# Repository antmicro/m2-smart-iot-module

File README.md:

# M.2 Smart IoT Module

Copyright (c) 2020-2026 [Antmicro](https://www.antmicro.com)

## Overview

This project contains PCB design files of the smart IoT module in an M.2 form factor.
The module is an experimental platform that combines a programmable Nordic radio SoC with Google Coral Edge AI accelerator.
The design files were prepared in KiCad.

## Repository structure

The main repository directory contains KiCad PCB project files, a LICENSE and a README.
The remaining files are stored in the following directories:

* ``lib`` - contains the component libraries
* ``img`` - contains graphics for this README
* ``fab`` - contains overrides for board visualization

## Key Features

* Google Coral Edge TPU Accelerator Module
* Nordic Semiconductor nRF52840 Radio SoC
* On-board PCIe-USB bridge
* On-board FTDI chip for nRF52840 programming, debugging and serial communication
* M.2 key B+M form factor 
* 22 x 80 mm (0.87 x 3.15 inch) PCB outline

## License

[Apache-2.0](LICENSE)

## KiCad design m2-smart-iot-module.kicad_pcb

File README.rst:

====================
M.2 Smart IoT Module
====================

Copyright (c) 2020-2021 `Antmicro <https://www.antmicro.com>`_

.. figure:: img/m2-smart-iot-module.png

Overview
--------

This repository contains design files of the smart IoT module in an M.2 form factor.
The module is an experimental platform that combines a programmable Nordic radio SoC with Google Coral Edge AI accelerator.
The design files were prepared in KiCad.
An initial production release for the design was fabricated as prototypes and these are now being tested.

Repository structure
--------------------
The main repository directory contains KiCad PCB project files, a LICENSE and README.
The remaining files are stored in the following directories:

* ``lib`` - contains the component libraries
* ``img`` - contains graphics for this README

Key Features
------------

* M.2 key B+M form factor 
* on-board PCIe-USB bridge
* Nordic Semiconductor nRF52840 Radio SoC
* Google Coral Edge TPU Accelerator Module

Block diagram
-------------

.. figure:: img/block-diagram.jpg

License
=======

`Apache-2.0 <LICENSE>`_

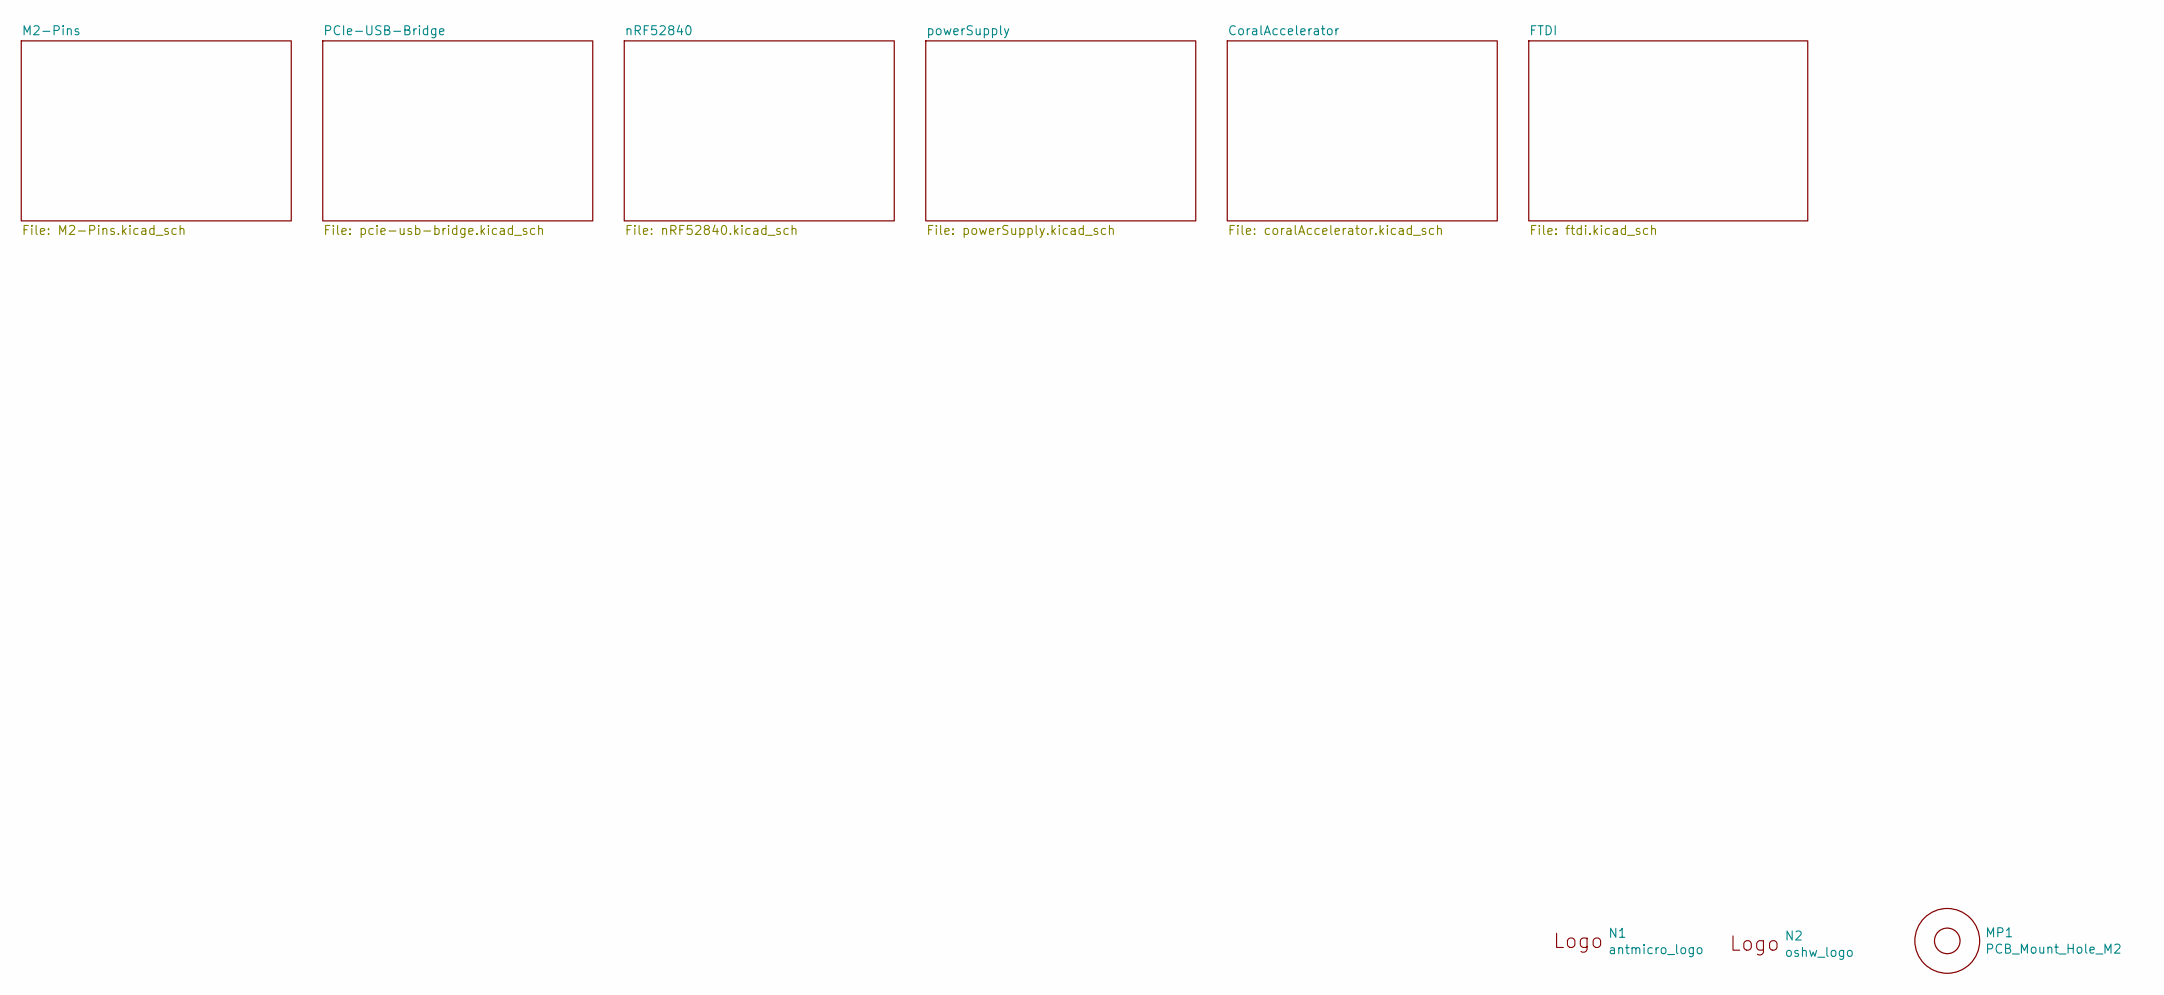
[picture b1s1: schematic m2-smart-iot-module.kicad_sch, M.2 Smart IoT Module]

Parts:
MP1: PCB_Mount_Hole_M2; M.2-Stud
N1: antmicro_logo; antmicro-logo_scaled_12mm
N2: oshw_logo; OSHW-Logo2_7.3x6mm_Copper_Mask

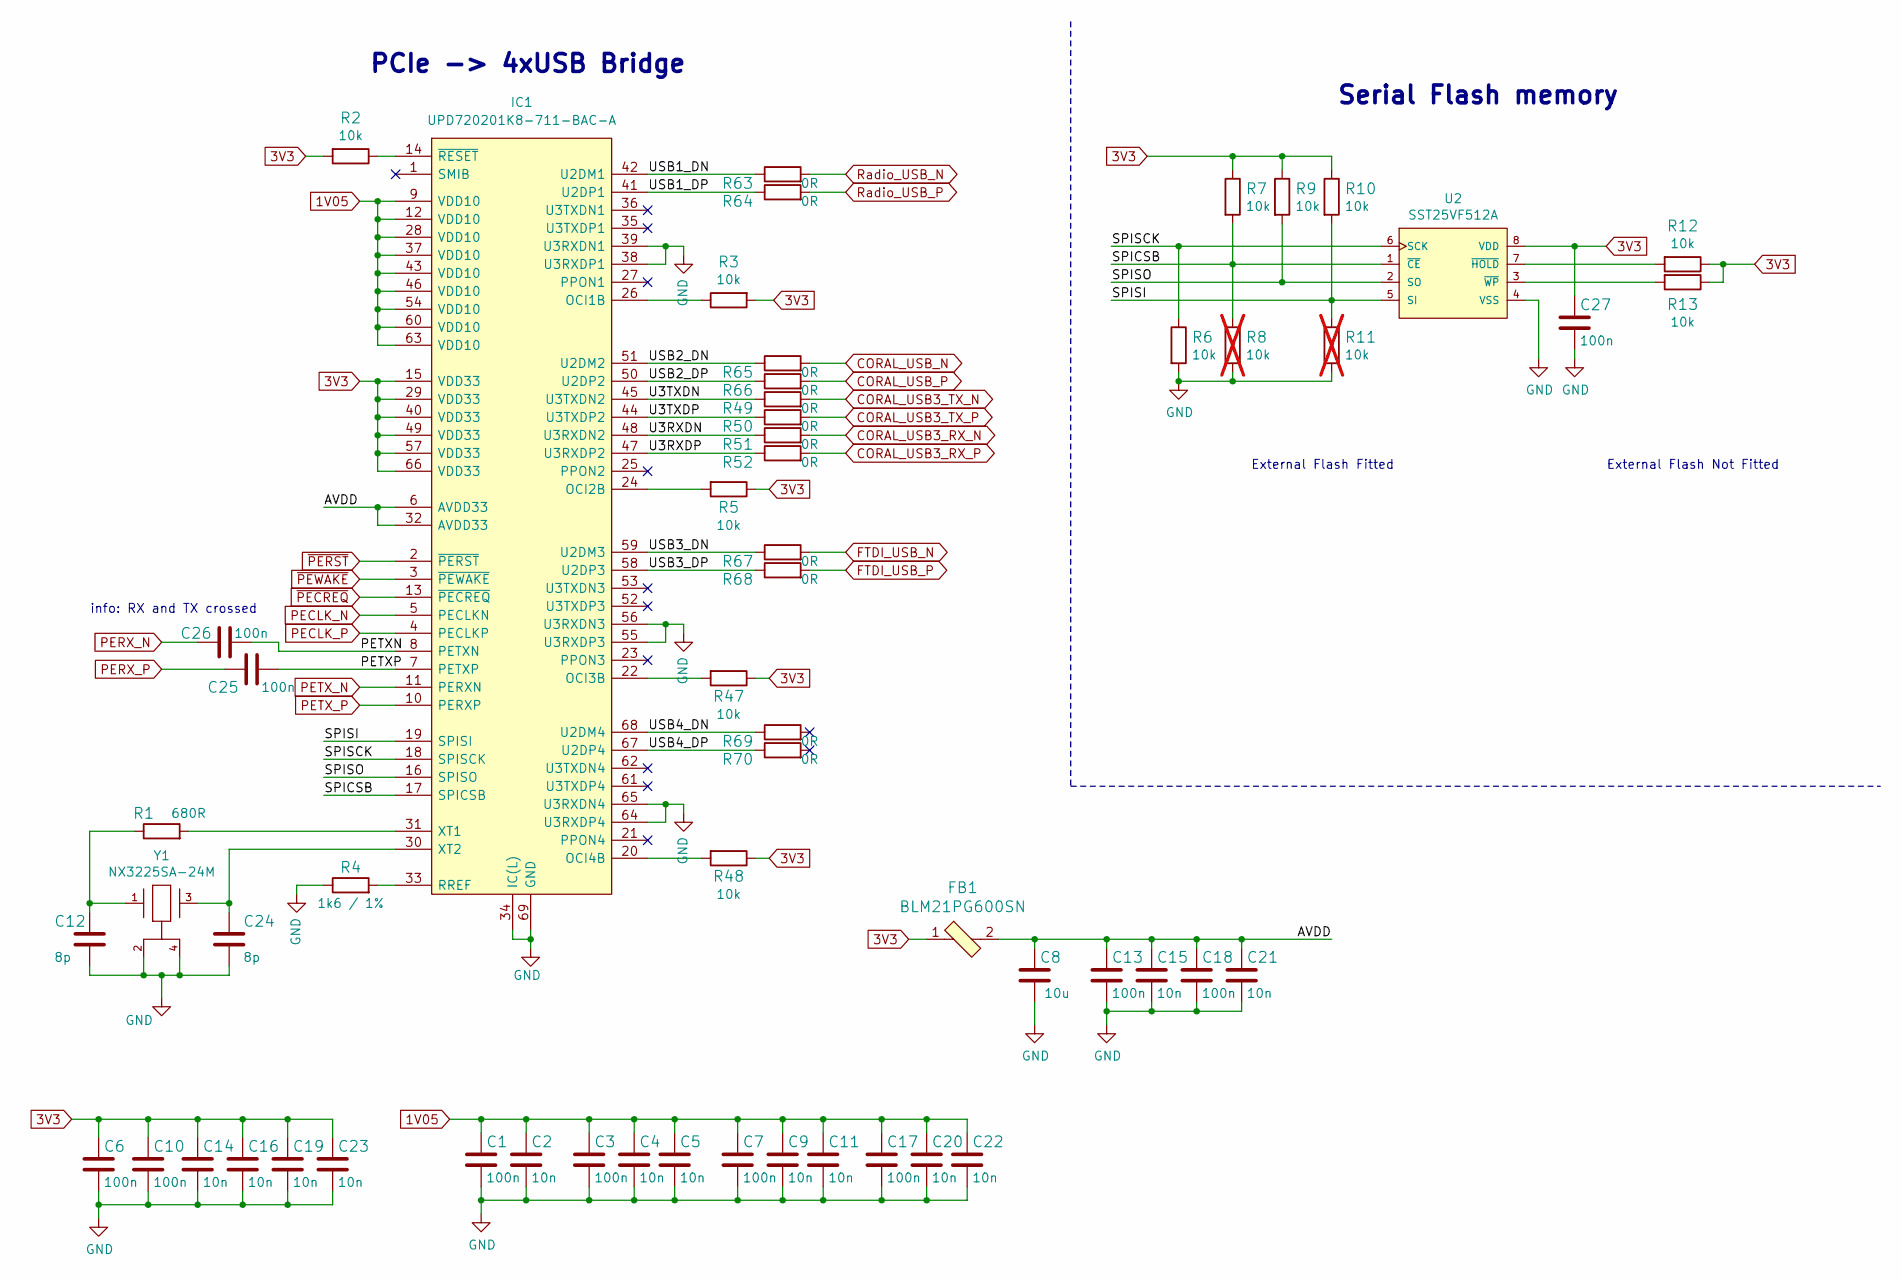
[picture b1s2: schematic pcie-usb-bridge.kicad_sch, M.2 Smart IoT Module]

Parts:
C1, C3, C6, C7, C10, C13, C17, C18, C25, C26, C27: C_100n_0402; 0402-cap; MPN GRM155R61H104KE14D
C2, C4, C5, C9, C11, C14, C15, C16, C19, C20, C21, C22, C23: C_10n_0402; 0402-cap; MPN 04025G103ZAT2A
C8: C_10u_0805; 0805-cap; MPN 160R15X106KV4E
C12, C24: C_8p_0402; 0402-cap; MPN CGA2B2C0G1H080D050BA
FB1: BLM21PG600SN; 0805-res; MPN BLM21PG600SN1
IC1: UPD720201K8-711-BAC-A; QFN40P800X800X90-69N-D; MPN UPD720201K8-711-BAC-A
R1: R_680R_0402; 0402-res; MPN MCWR04X6800FTL
R2, R3, R5, R6, R7, R9, R10, R12, R13: R_10k_0402; 0402-res; MPN CRCW040210K0FKEDHP
R4: R_1k6_0402; 0402-res; MPN MCWR04X1601FTL
R8, R11: R_10k_0402; 0402-res; MPN CRCW040210K0FKEDHP; not fitted
R47, R48: 0402-res; MPN CRCW040210K0FKEDHP
R49, R50, R51, R52, R63, R64, R65, R66, R67, R68, R69, R70: R_0R_0402; 0402-res; MPN ERJ2GE0R00X
U2: SST25VF512A; SOIC8-SST25VF512A-33-4I-SAE-Level_B; MPN SST25VF512A-33-4I-SAE
Y1: NX3225SA-24M; NDK-NX3225SA-0-0-MFG; MPN NX3225SA-24.000M-STD-CSR-3

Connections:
1V05: C1.1, C2.1, C3.1, C4.1, C5.1, C7.1, C9.1, C11.1, C17.1, C20.1, C22.1, IC1.9 (VDD10), IC1.12 (VDD10), IC1.28 (VDD10), IC1.37 (VDD10), IC1.43 (VDD10), IC1.46 (VDD10), IC1.54 (VDD10), IC1.60 (VDD10), IC1.63 (VDD10); also elsewhere on the board
3V3: C6.1, C10.1, C14.1, C16.1, C19.1, C23.1, C27.1, FB1.1, IC1.15 (VDD33), IC1.29 (VDD33), IC1.40 (VDD33), IC1.49 (VDD33), IC1.57 (VDD33), IC1.66 (VDD33), R2.2, R3.2, R5.1, R7.1, R9.1, R10.1, R12.1, R13.1, R47.1, R48.1, U2.8 (VDD); also elsewhere on the board
/PCIe-USB-Bridge/AVDD: C8.1, C13.1, C15.1, C18.1, C21.1, FB1.2, IC1.6 (AVDD33), IC1.32 (AVDD33)
/PCIe-USB-Bridge/PETXN: C26.1, IC1.8 (PETXN)
/PCIe-USB-Bridge/PETXP: C25.1, IC1.7 (PETXP)
/PCIe-USB-Bridge/SPICSB: IC1.17 (SPICSB), R7.2, R8.1, U2.1 (~CE)
/PCIe-USB-Bridge/SPISCK: IC1.18 (SPISCK), R6.1, U2.6 (SCK)
/PCIe-USB-Bridge/SPISI: IC1.19 (SPISI), R10.2, R11.1, U2.5 (SI)
/PCIe-USB-Bridge/SPISO: IC1.16 (SPISO), R9.2, U2.2 (SO)
/PCIe-USB-Bridge/U3RXDN: IC1.48 (U3RXDN2), R51.1
/PCIe-USB-Bridge/U3RXDP: IC1.47 (U3RXDP2), R52.1
/PCIe-USB-Bridge/U3TXDN: IC1.45 (U3TXDN2), R49.1
/PCIe-USB-Bridge/U3TXDP: IC1.44 (U3TXDP2), R50.1
/PCIe-USB-Bridge/USB1_DN: IC1.42 (U2DM1), R63.1
/PCIe-USB-Bridge/USB1_DP: IC1.41 (U2DP1), R64.1
/PCIe-USB-Bridge/USB2_DN: IC1.51 (U2DM2), R65.1
/PCIe-USB-Bridge/USB2_DP: IC1.50 (U2DP2), R66.1
/PCIe-USB-Bridge/USB3_DN: IC1.59 (U2DM3), R67.1
/PCIe-USB-Bridge/USB3_DP: IC1.58 (U2DP3), R68.1
/PCIe-USB-Bridge/USB4_DN: IC1.68 (U2DM4), R69.1
/PCIe-USB-Bridge/USB4_DP: IC1.67 (U2DP4), R70.1
CORAL_USB3_RX_N: R51.2
CORAL_USB3_RX_P: R52.2
CORAL_USB3_TX_N: R49.2
CORAL_USB3_TX_P: R50.2
CORAL_USB_N: R65.2; also elsewhere on the board
CORAL_USB_P: R66.2; also elsewhere on the board
FTDI_USB_N: R67.2; also elsewhere on the board
FTDI_USB_P: R68.2; also elsewhere on the board
GND: C1.2, C2.2, C3.2, C4.2, C5.2, C6.2, C7.2, C8.2, C9.2, C10.2, C11.2, C12.2, C13.2, C14.2, C15.2, C16.2, C17.2, C18.2, C19.2, C20.2, C21.2, C22.2, C23.2, C24.2, C27.2, IC1.34 (IC(L)), IC1.38 (U3RXDP1), IC1.39 (U3RXDN1), IC1.55 (U3RXDP3), IC1.56 (U3RXDN3), IC1.64 (U3RXDP4), IC1.65 (U3RXDN4), IC1.69 (GND), R4.1, R6.2, R8.2, R11.2, U2.4 (VSS), Y1.2 (GND), Y1.4 (GND); also elsewhere on the board
unnamed: C12.1, R1.1, Y1.1
unnamed: C24.1, IC1.30 (XT2), Y1.3
unnamed: IC1.14 (~RESET), R2.1
unnamed: IC1.20 (OCI4B), R48.2
unnamed: IC1.22 (OCI3B), R47.2
unnamed: IC1.24 (OCI2B), R5.2
unnamed: IC1.26 (OCI1B), R3.1
unnamed: IC1.31 (XT1), R1.2
unnamed: IC1.33 (RREF), R4.2
unnamed: R12.2, U2.7 (~HOLD)
unnamed: R13.2, U2.3 (~WP)
PECLK_N: IC1.5 (PECLKN); also elsewhere on the board
PECLK_P: IC1.4 (PECLKP); also elsewhere on the board
PERX_N: C26.2; also elsewhere on the board
PERX_P: C25.2; also elsewhere on the board
PETX_N: IC1.11 (PERXN); also elsewhere on the board
PETX_P: IC1.10 (PERXP); also elsewhere on the board
Radio_USB_N: R63.2; also elsewhere on the board
Radio_USB_P: R64.2; also elsewhere on the board
~PECREQ: IC1.13 (~PECREQ); also elsewhere on the board
~PERST: IC1.2 (~PERST); also elsewhere on the board
~PEWAKE: IC1.3 (~PEWAKE); also elsewhere on the board

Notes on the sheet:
Serial Flash memory
External Flash Not Fitted
PCIe -> 4xUSB Bridge
External Flash Fitted
info: RX and TX crossed

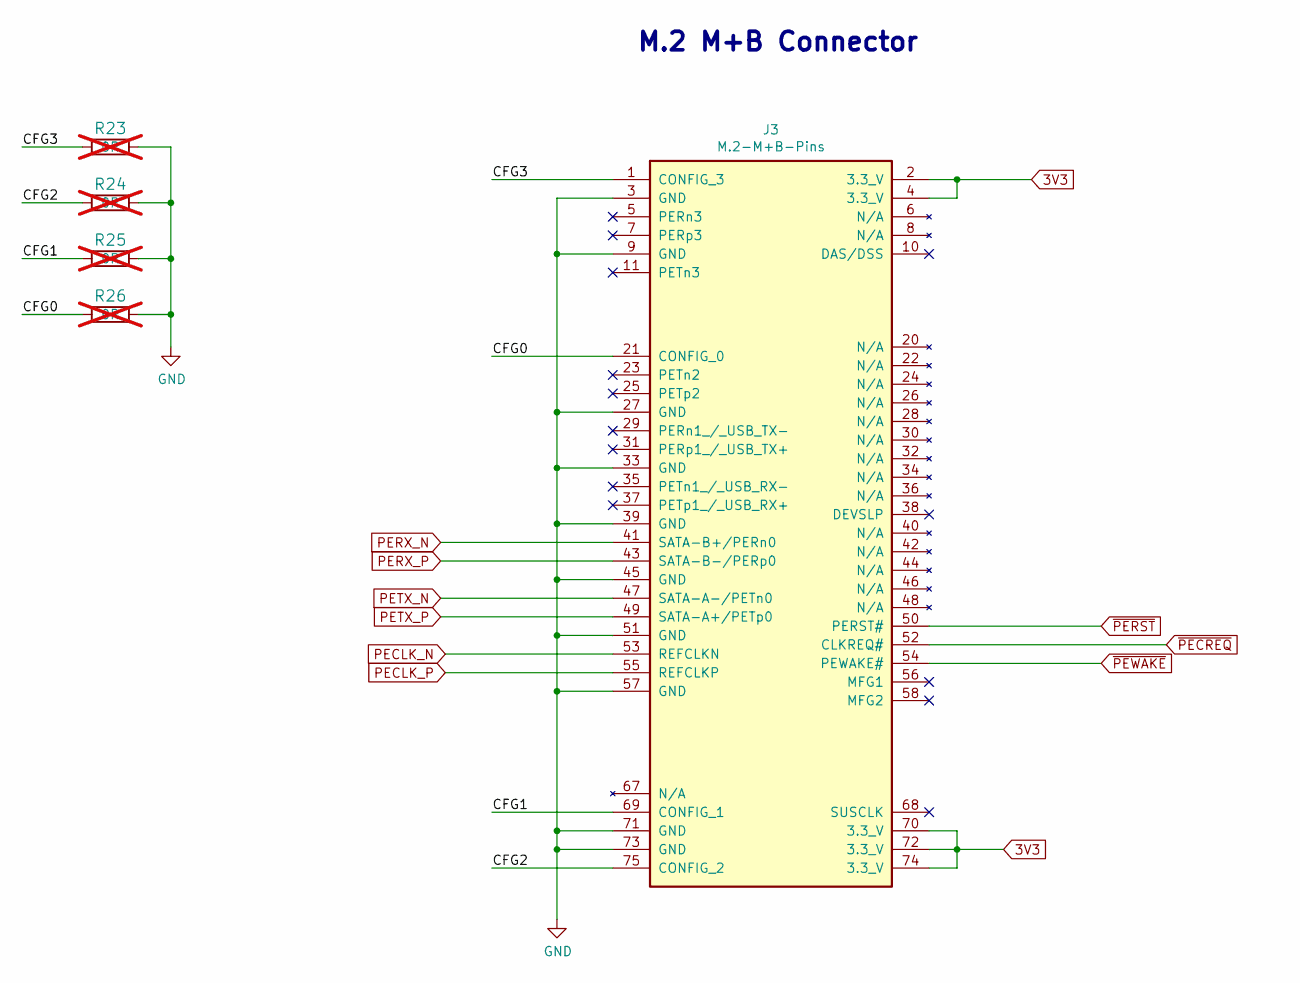
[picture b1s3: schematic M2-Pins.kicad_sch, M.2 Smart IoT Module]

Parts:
J3: M.2-M+B-Pins; M.2-M+B-Keys
R23, R24, R25, R26: R_0R_0402; 0402-res; MPN ERJ2GE0R00X; not fitted

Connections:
3V3: J3.2 (3.3_V), J3.4 (3.3_V), J3.70 (3.3_V), J3.72 (3.3_V), J3.74 (3.3_V); also elsewhere on the board
/M2-Pins/CFG0: J3.21 (CONFIG_0), R26.1
/M2-Pins/CFG1: J3.69 (CONFIG_1), R25.1
/M2-Pins/CFG2: J3.75 (CONFIG_2), R24.1
/M2-Pins/CFG3: J3.1 (CONFIG_3), R23.1
GND: J3.3 (GND), J3.9 (GND), J3.27 (GND), J3.33 (GND), J3.39 (GND), J3.45 (GND), J3.51 (GND), J3.57 (GND), J3.71 (GND), J3.73 (GND), R23.2, R24.2, R25.2, R26.2; also elsewhere on the board
PECLK_N: J3.53 (REFCLKN); also elsewhere on the board
PECLK_P: J3.55 (REFCLKP); also elsewhere on the board
PERX_N: J3.41 (SATA-B+/PERn0); also elsewhere on the board
PERX_P: J3.43 (SATA-B-/PERp0); also elsewhere on the board
PETX_N: J3.47 (SATA-A-/PETn0); also elsewhere on the board
PETX_P: J3.49 (SATA-A+/PETp0); also elsewhere on the board
~PECREQ: J3.52 (CLKREQ#); also elsewhere on the board
~PERST: J3.50 (PERST#); also elsewhere on the board
~PEWAKE: J3.54 (PEWAKE#); also elsewhere on the board

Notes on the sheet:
M.2 M+B Connector

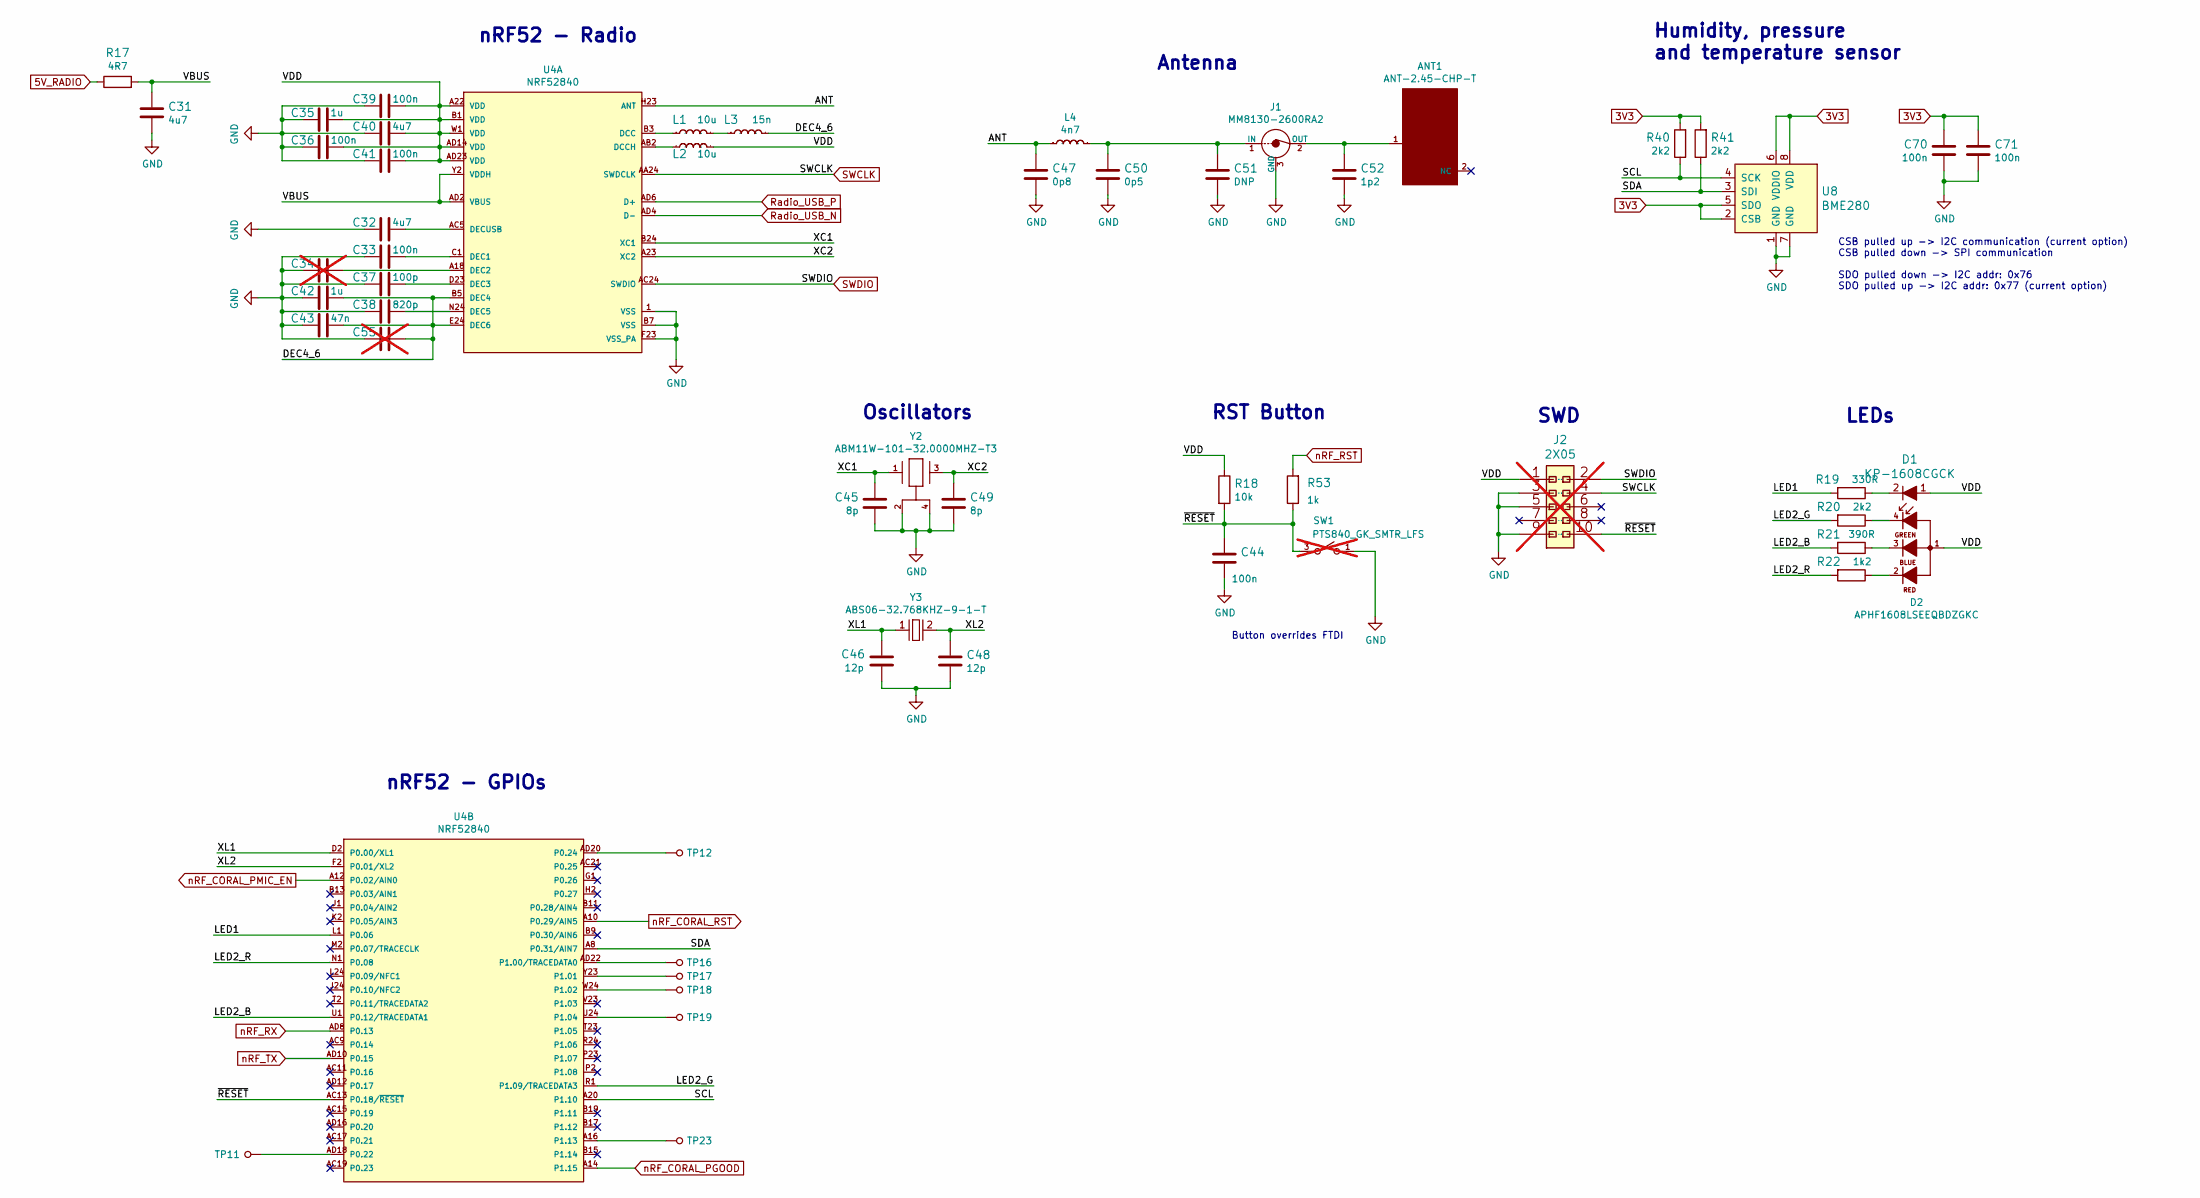
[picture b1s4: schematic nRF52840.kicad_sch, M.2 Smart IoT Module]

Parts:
ANT1: ANT-2.45-CHP-T; Linx-ANT-2.45-CHP-T-MFG; MPN ANT-2.45-CHP-T
C31, C32, C40: C_4u7_0402; 0402-cap; MPN GRM155R61A475MEAAD
C33, C36, C39, C41, C44, C70, C71: C_100n_0402; 0402-cap; MPN GRM155R61H104KE14D
C34, C55: C_100n_0402; 0402-cap; MPN 0402X104K6R3CT; not fitted
C35, C42: C_1u_0402; 0402-cap; MPN C1005X6S1A105K050BC
C37: C_100p_0402; 0402-cap; MPN 0402N101J500CT
C38: C_820p_0402; 0402-cap; MPN CGA2B2C0G1H821J050BA
C43: C_47n_0402; 0402-cap; MPN MC0402X473K160CT
C45, C49: C_8p_0402; 0402-cap; MPN CGA2B2C0G1H080D050BA
C46, C48: C_12p_0402; 0402-cap; MPN CGA2B2C0G1H120J050BA
C47: C_0p8_0402; 0402-cap; MPN GJM1555C1HR80WB01D
C50: C_0p5_0402; 0402-cap; MPN GJM1555C1HR50WB01D
C51: RF_Capacitor; 0402-cap
C52: C_1p2_0402; 0402-cap; MPN GJM1555C1H1R2WB01D
D1: KP-1608CGCK; LED0603; MPN KP-1608CGCK
D2: APHF1608LSEEQBDZGKC; LED_APHF1608LSEEQBDZGKC; MPN APHF1608LSEEQBDZGKC
J1: MM8130-2600RA2; Murata-MM8130-2600RA2-MFG; MPN MM8130-2600RA2
J2: 2X05; ARM_SWD; MPN SHF-105-01-L-D-SM; not fitted
L1: L_10u_250mA_0603; 0603-res; MPN MLZ1608M100WTD25
L2: L_10u_80mA_0603; 0603-res; MPN LBMF1608T100K
L3: L_15n_0402; 0402-res; MPN HK100515NJ-T
L4: L_4n7_0402; 0402-res; MPN MCFT000004
R17: R_4R7_0402; 0402-res; MPN ERJ2GEJ4R7X
R18: R_10k_0402; 0402-res; MPN CRCW040210K0FKEDHP
R19: R_330R_0402; 0402-res; MPN ERJ2RKF3300X
R20, R40, R41: R_2k2_0402; 0402-res; MPN RC0402FR-072K2L
R21: R_390R_0402; 0402-res; MPN ERJ2RKF3900X
R22: R_1k2_0402; 0402-res; MPN ERJ2RKF1201X
R53: R_1k_0402; 0402-res; MPN CR0402-FX-1001GLF
SW1: PTS840_GK_SMTR_LFS; CK-PTS840_GK_SMTR_LFS-0; MPN PTS840 GK SMTR LFS; not fitted
TP11, TP12, TP16, TP17, TP18, TP19, TP23: TP_SMD1MM; Testpoint_smd_1mm
U4: NRF52840; Nordic_Semiconductor-NRF52840-QIAA-R-0-0-MFG; MPN NRF52840-QIAA-R
U8: BME280; Pressure_Sensor_LGA-8_2.5x2.5mm_BME280; MPN BME280
Y2: ABM11W-101-32.0000MHZ-T3; Abracon-ABM11W-0-0-0; MPN ABM11W-101-32.0000MHZ-T3
Y3: ABS06-32.768KHZ-9-1-T; Abracon-ABS06-32.768KHZ-T-0; MPN ABS06-32.768KHZ-9-1-T

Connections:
3V3: C70.2, C71.1, R40.2, R41.2, U8.2 (CSB), U8.5 (SDO), U8.6 (VDDIO), U8.8 (VDD); also elsewhere on the board
5V_RADIO: R17.1; also elsewhere on the board
/nRF52840/ANT: C47.1, L4.1, U4.H23 (ANT)
/nRF52840/DEC4_6: C42.1, C43.1, C55.1, L3.2, U4.B5 (DEC4), U4.E24 (DEC6)
/nRF52840/LED1: R19.2, U4.L1 (P0.06)
/nRF52840/LED2_B: R21.2, U4.U1 (P0.12/TRACEDATA1)
/nRF52840/LED2_G: R20.2, U4.R1 (P1.09/TRACEDATA3)
/nRF52840/LED2_R: R22.2, U4.N1 (P0.08)
/nRF52840/SCL: R40.1, U4.A20 (P1.10), U8.4 (SCK)
/nRF52840/SDA: R41.1, U4.A8 (P0.31/AIN7), U8.3 (SDI)
/nRF52840/VBUS: C31.1, R17.2, U4.AD2 (VBUS), U4.Y2 (VDDH)
/nRF52840/VDD: C35.1, C36.1, C39.1, C40.1, C41.1, D1.1, D2.1, J2.1, L2.2, R18.1, U4.A22 (VDD), U4.AD14 (VDD), U4.AD23 (VDD), U4.B1 (VDD), U4.W1 (VDD)
/nRF52840/XC1: C45.1, U4.B24 (XC1), Y2.1
/nRF52840/XC2: C49.1, U4.A23 (XC2), Y2.3
/nRF52840/XL1: C46.1, U4.D2 (P0.00/XL1), Y3.1
/nRF52840/XL2: C48.1, U4.F2 (P0.01/XL2), Y3.2
/nRF52840/~RESET: C44.1, J2.10, R18.2, R53.1, SW1.3, SW1.4, U4.AC13 (P0.18/~RESET)
GND: C31.2, C32.2, C33.2, C34.2, C35.2, C36.2, C37.2, C38.2, C39.2, C40.2, C41.2, C42.2, C43.2, C44.2, C45.2, C46.2, C47.2, C48.2, C49.2, C50.2, C51.2, C52.2, C55.2, C70.1, C71.2, J1.3 (GND), J1.4 (GND), J1.5 (GND), J1.6 (GND), J2.3, J2.5, J2.9, SW1.1, SW1.2, U4.1 (VSS), U4.B7 (VSS), U4.F23 (VSS_PA), U8.1 (GND), U8.7 (GND), Y2.2 (GND), Y2.4 (GND); also elsewhere on the board
unnamed: ANT1.1 (FEED), C52.1, J1.2 (OUT)
unnamed: C32.1, U4.AC5 (DECUSB)
unnamed: C33.1, U4.C1 (DEC1)
unnamed: C34.1, U4.A18 (DEC2)
unnamed: C37.1, U4.D23 (DEC3)
unnamed: C38.1, U4.N24 (DEC5)
unnamed: C50.1, C51.1, J1.1 (IN), L4.2
unnamed: D1.2, R19.1
unnamed: D2.2, R22.1
unnamed: D2.3, R21.1
unnamed: D2.4, R20.1
unnamed: L1.1, U4.B3 (DCC)
unnamed: L1.2, L3.1
unnamed: L2.1, U4.AB2 (DCCH)
unnamed: TP11.1, U4.AD18 (P0.22)
unnamed: TP12.1, U4.AD20 (P0.24)
unnamed: TP16.1, U4.AD22 (P1.00/TRACEDATA0)
unnamed: TP17.1, U4.Y23 (P1.01)
unnamed: TP18.1, U4.W24 (P1.02)
unnamed: TP19.1, U4.U24 (P1.04)
unnamed: TP23.1, U4.A16 (P1.13)
Radio_USB_N: U4.AD4 (D-); also elsewhere on the board
Radio_USB_P: U4.AD6 (D+); also elsewhere on the board
SWCLK: J2.4, U4.AA24 (SWDCLK); also elsewhere on the board
SWDIO: J2.2, U4.AC24 (SWDIO); also elsewhere on the board
nRF_CORAL_PGOOD: U4.A14 (P1.15); also elsewhere on the board
nRF_CORAL_PMIC_EN: U4.A12 (P0.02/AIN0); also elsewhere on the board
nRF_CORAL_RST: U4.A10 (P0.29/AIN5); also elsewhere on the board
nRF_RST: R53.2; also elsewhere on the board
nRF_RX: U4.AD8 (P0.13); also elsewhere on the board
nRF_TX: U4.AD10 (P0.15); also elsewhere on the board

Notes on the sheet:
Button overrides FTDI
CSB pulled up -> I2C communication (current option) CSB pulled down -> SPI communication SDO pulled down -> I2C addr: 0x76 SDO pulled up -> I2C addr: 0x77 (current option)
Antenna
Oscillators
nRF52 - GPIOs
LEDs
RST Button
nRF52 - Radio
Humidity, pressure and temperature sensor
SWD

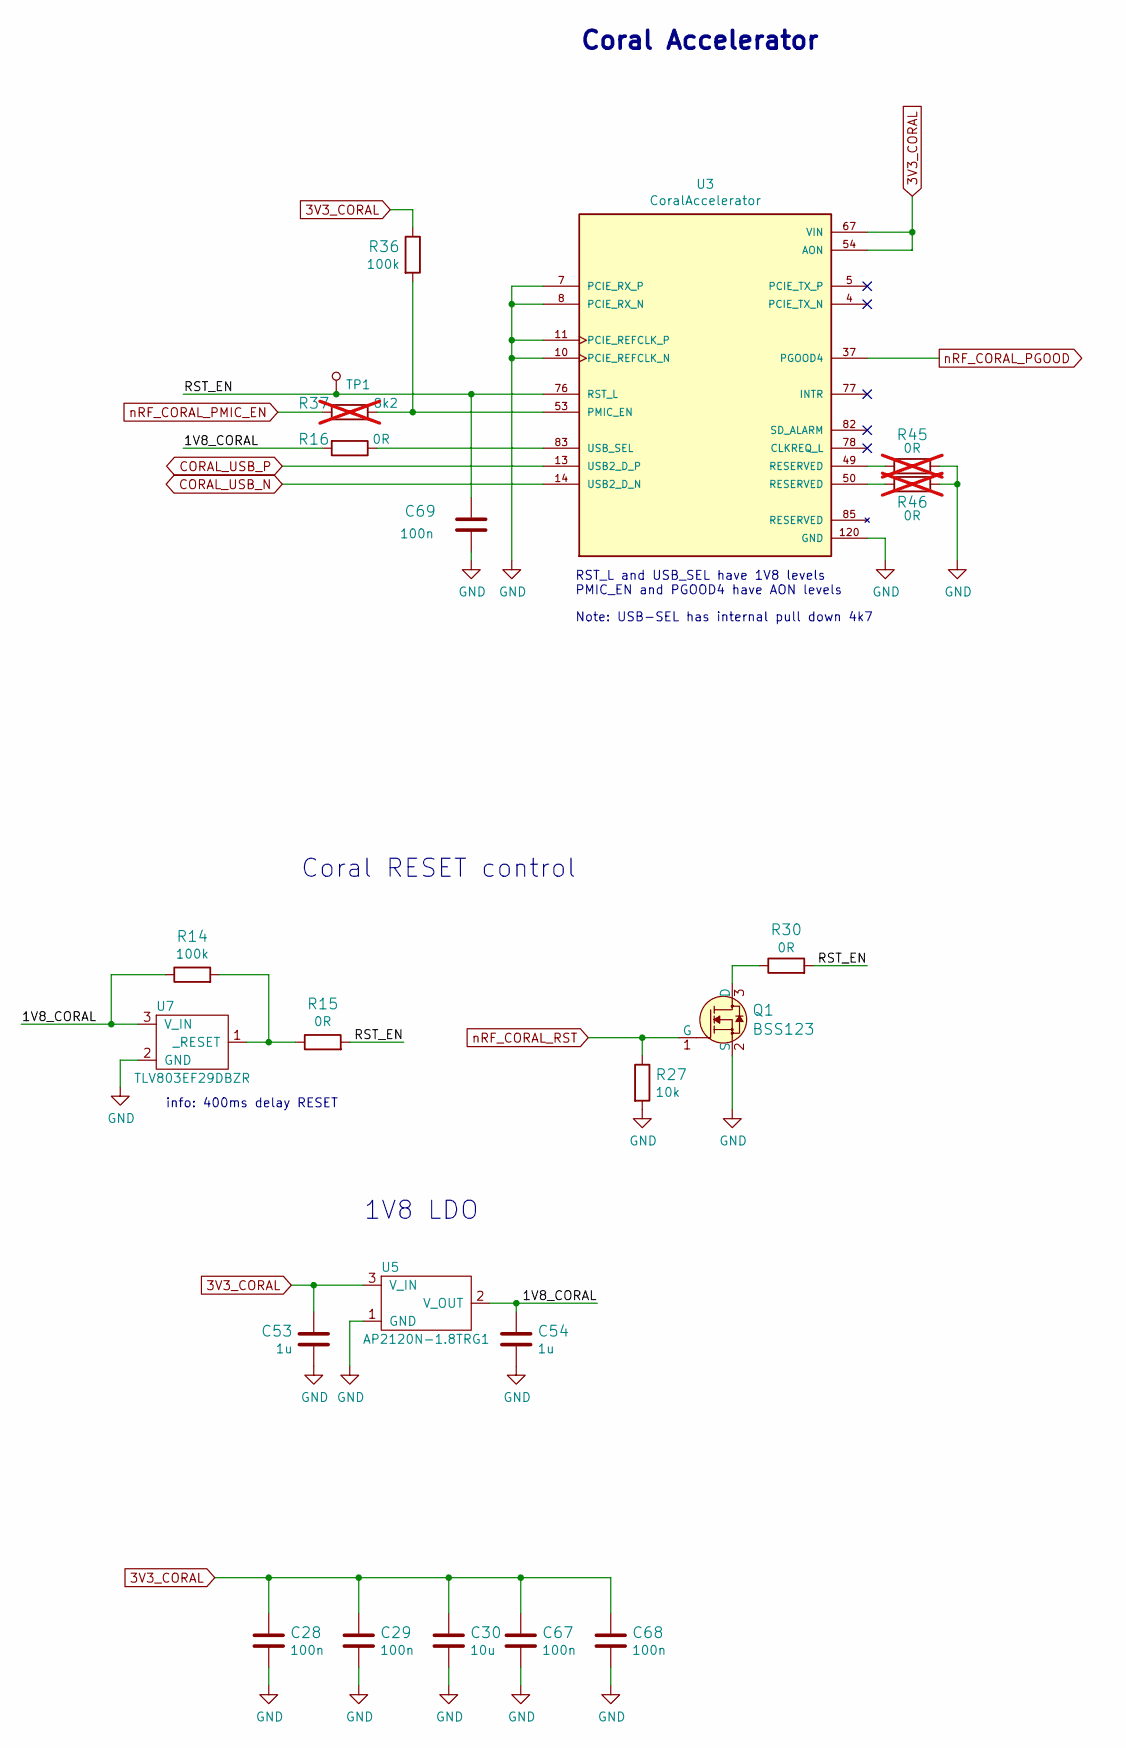
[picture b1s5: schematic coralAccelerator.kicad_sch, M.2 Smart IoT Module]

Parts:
C28, C29, C67, C68, C69: C_100n_0402; 0402-cap; MPN GRM155R61H104KE14D
C30: C_10u_0805; 0805-cap; MPN 160R15X106KV4E
C53, C54: C_1u_0402; 0402-cap; MPN C1005X6S1A105K050BC
Q1: BSS123; SOT-23-3; MPN BSS123
R14, R36: R_100k_0402; 0402-res; MPN CRCW0402100KFKEDHP
R15, R16, R30: R_0R_0402; 0402-res; MPN ERJ2GE0R00X
R27: R_10k_0402; 0402-res; MPN CRCW040210K0FKEDHP
R37: R_8k2_0402; 0402-res; MPN ERJ2RKF8201X; not fitted
R45, R46: R_0R_0402; 0402-res; MPN ERJ2GE0R00X; not fitted
TP1: TP_SMD1MM; Testpoint_smd_1mm
U3: CoralAccelerator; MODULE_G313-06329-00; MPN G313-06329-00
U5: AP2120N-1.8TRG1; SOT-23-3; MPN AP2120N-1.8TRG1
U7: TLV803EF29DBZR; SOT-23-3; MPN TLV803EF29DBZR

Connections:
3V3_CORAL: C28.1, C29.1, C30.1, C53.1, C67.1, C68.1, R36.1, U3.54 (AON), U3.56 (VIN), U3.57 (VIN), U3.58 (VIN), U3.59 (VIN), U3.60 (VIN), U3.61 (VIN), U3.62 (VIN), U3.63 (VIN), U3.64 (VIN), U3.65 (VIN), U3.66 (VIN), U3.67 (VIN), U5.3 (V_IN); also elsewhere on the board
/CoralAccelerator/1V8_CORAL: C54.1, R14.1, R16.2, U5.2 (V_OUT), U7.3 (V_IN)
/CoralAccelerator/RST_EN: C69.1, R15.2, R30.2, TP1.1, U3.76 (RST_L)
CORAL_USB_N: U3.14 (USB2_D_N); also elsewhere on the board
CORAL_USB_P: U3.13 (USB2_D_P); also elsewhere on the board
GND: C28.2, C29.2, C30.2, C53.2, C54.2, C67.2, C68.2, C69.2, Q1.2 (S), R27.2, R45.2, R46.2, U3.1 (GND), U3.2 (GND), U3.3 (GND), U3.6 (GND), U3.7 (PCIE_RX_P), U3.8 (PCIE_RX_N), U3.9 (GND), U3.10 (PCIE_REFCLK_N), U3.11 (PCIE_REFCLK_P), U3.12 (GND), U3.15 (GND), U3.16 (GND), U3.17 (GND), U3.18 (GND), U3.19 (GND), U3.20 (GND), U3.21 (GND), U3.22 (GND), U3.23 (GND), U3.24 (GND), U3.25 (GND), U3.26 (GND), U3.27 (GND), U3.28 (GND), U3.29 (GND), U3.30 (GND), U3.31 (GND), U3.32 (GND), U3.33 (GND), U3.34 (GND), U3.35 (GND), U3.36 (GND), U3.38 (GND), U3.39 (GND), U3.40 (GND), U3.41 (GND), U3.42 (GND), U3.43 (GND), U3.44 (GND), U3.45 (GND), U3.46 (GND), U3.47 (GND), U3.48 (GND), U3.51 (GND), U3.55 (GND), U3.68 (GND), U3.69 (GND), U3.70 (GND), U3.71 (GND), U3.72 (GND), U3.73 (GND), U3.74 (GND), U3.75 (GND), U3.79 (GND), U3.80 (GND), U3.81 (GND), U3.86 (GND), U3.87 (GND), U3.88 (GND), U3.89 (GND), U3.90 (GND), U3.91 (GND), U3.92 (GND), U3.93 (GND), U3.94 (GND), U3.95 (GND), U3.96 (GND), U3.97 (GND), U3.98 (GND), U3.99 (GND), U3.100 (GND), U3.101 (GND), U3.102 (GND), U3.103 (GND), U3.104 (GND), U3.105 (GND), U3.106 (GND), U3.107 (GND), U3.108 (GND), U3.109 (GND), U3.110 (GND), U3.111 (GND), U3.112 (GND), U3.113 (GND), U3.114 (GND), U3.115 (GND), U3.116 (GND), U3.117 (GND), U3.118 (GND), U3.119 (GND), U3.120 (GND), U5.1 (GND), U7.2 (GND); also elsewhere on the board
unnamed: Q1.3 (D), R30.1
unnamed: R14.2, R15.1, U7.1 (_RESET)
unnamed: R16.1, U3.83 (USB_SEL)
unnamed: R36.2, R37.1, U3.53 (PMIC_EN)
unnamed: R45.1, U3.49 (RESERVED)
unnamed: R46.1, U3.50 (RESERVED)
nRF_CORAL_PGOOD: U3.37 (PGOOD4); also elsewhere on the board
nRF_CORAL_PMIC_EN: R37.2; also elsewhere on the board
nRF_CORAL_RST: Q1.1 (G), R27.1; also elsewhere on the board

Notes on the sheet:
RST_L and USB_SEL have 1V8 levels PMIC_EN and PGOOD4 have AON levels
Coral Accelerator
Coral RESET control
Note: USB-SEL has internal pull down 4k7
info: 400ms delay RESET
1V8 LDO
